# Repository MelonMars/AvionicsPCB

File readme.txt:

I think I'm doing this right, idk

2 Potentiometers: One is wind direction, other is wind intensity, max of 35 kts
LED Grid:
Top row is a turn coordinator, keep the white led in the middle, led moves in a direction that is prescriptives, use rudder coordinating with that side to correct a slip
Second from top row is altitude. Each dot is 1000 feet, going from dark to bright white, through grey for the altitude within 1000 feet
Next row is altitude in 10s of feet.
Altitudes are determined from barometric pressure, so are MSL and susceptible to temperature problems

Problem with the turn coordinator is idk how to actually have the turn coordinator figure out anything abt the turn. i BELIEVE that if the 3 axis accelerometer should be able to, as if it doesn't register a change while your turning, that means your CG(?) (I think CG is what the turn coordinator checks for slips, but once again I'm not sure) hasn't really changed, and you're going alright.

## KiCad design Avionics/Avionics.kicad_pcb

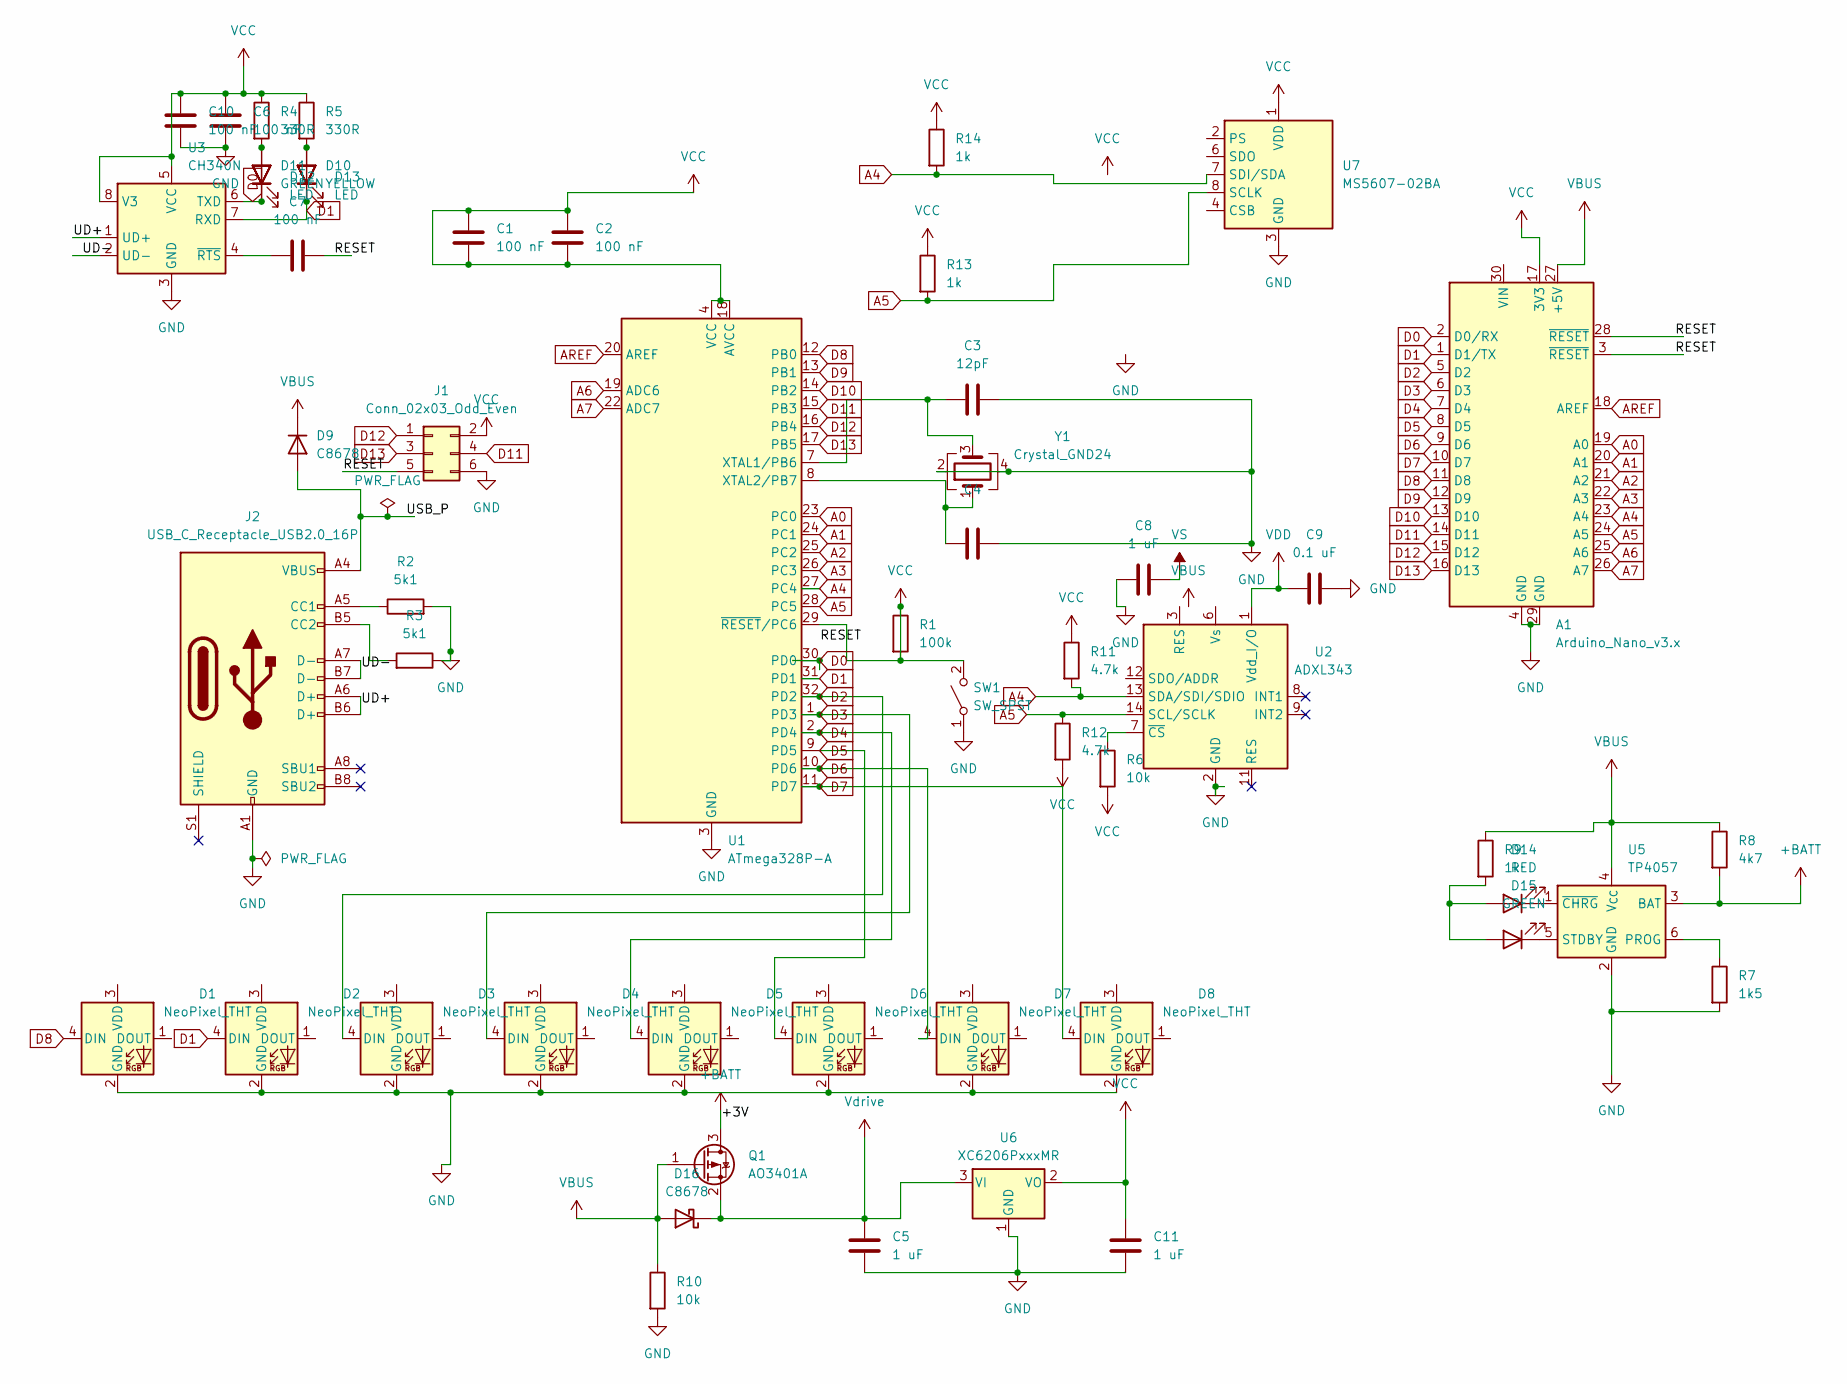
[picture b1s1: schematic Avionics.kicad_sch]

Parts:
A1: Arduino_Nano_v3.x; Arduino_Nano_WithMountingHoles
C1, C2, C6, C7, C10: 100 nF; C_0805_2012Metric_Pad1.18x1.45mm_HandSolder; LCSC C49678
C3, C4: 12pF; C_0805_2012Metric_Pad1.18x1.45mm_HandSolder; LCSC C1792
C5, C8, C11: 1 uF; C_0805_2012Metric_Pad1.18x1.45mm_HandSolder; LCSC C111768
C9: 0.1 uF; C_0805_2012Metric_Pad1.18x1.45mm_HandSolder; LCSC C49678
D1, D2, D3, D4, D5, D6, D7, D8: NeoPixel_THT; LED_WS2812_PLCC6_5.0x5.0mm_P1.6mm; LCSC C5378720
D9: C8678; D_SMC_Handsoldering; LCSC C8678
D10: YELLOW; D_SMC_Handsoldering; LCSC C2296
D11, D15: GREEN; D_1206_3216Metric_Pad1.42x1.75mm_HandSolder; LCSC C2297
D12, D13: LED; D_1206_3216Metric_Pad1.42x1.75mm_HandSolder; LCSC C2297
D14: RED; D_1206_3216Metric_Pad1.42x1.75mm_HandSolder; LCSC C101927
D16: C8678; D_SMA; LCSC C8678
J1: Conn_02x03_Odd_Even; PinHeader_2x03_P2.54mm_Vertical; LCSC C65114
J2: USB_C_Receptacle_USB2.0_16P; USB_C_Receptacle_Amphenol_12401548E4-2A; LCSC C2988369
Q1: AO3401A; SOT-23; LCSC C15127
R1: 100k; R_0805_2012Metric_Pad1.20x1.40mm_HandSolder; LCSC C101927
R2, R3: 5k1; R_0805_2012Metric_Pad1.20x1.40mm_HandSolder; LCSC C27834
R4, R5: 330R; R_0805_2012Metric_Pad1.20x1.40mm_HandSolder; LCSC C3016635
R6, R10: 10k; R_0805_2012Metric_Pad1.20x1.40mm_HandSolder; LCSC C17414
R7: 1k5; R_0805_2012Metric_Pad1.20x1.40mm_HandSolder; LCSC C416128
R8: 4k7; R_0805_2012Metric_Pad1.20x1.40mm_HandSolder; LCSC C2889530
R9, R13, R14: 1k; R_0805_2012Metric_Pad1.20x1.40mm_HandSolder; LCSC C17513
R11, R12: 4.7k; R_0805_2012Metric_Pad1.20x1.40mm_HandSolder; LCSC C245341
SW1: SW_SPST; SW_Push_1P1T_XKB_TS-1187A; LCSC C318884
U1: ATmega328P-A; TQFP-32_7x7mm_P0.8mm; LCSC C14877
U2: ADXL343; LGA-14_3x5mm_P0.8mm_LayoutBorder1x6y; LCSC C579453
U3: CH340N; SOP-8_3.9x4.9mm_P1.27mm; LCSC C2977777
U5: TP4057; TSOT-23-5; LCSC C725791
U6: XC6206PxxxMR; SOT-23-3; LCSC C2891841
U7: MS5607-02BA; LGA-8_3x5mm_P1.25mm; LCSC C97627
Y1: Crystal_GND24; Crystal_SMD_3225-4Pin_3.2x2.5mm_HandSoldering; LCSC C13738

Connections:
+BATT: Q1.3 (D), R8.2, U5.3 (BAT)
/RESET: A1.3 (~RESET), A1.28 (~RESET), C7.2, J1.5
/UD+: J2.A6 (D+), J2.B6 (D+), U3.1 (UD+)
/UD-: J2.A7 (D-), J2.B7 (D-), U3.2 (UD-)
/USB_P: D9.2 (A), J2.A4 (VBUS), J2.A9 (VBUS), J2.B4 (VBUS), J2.B9 (VBUS)
A0: A1.19 (A0), U1.23 (PC0)
A1: A1.20 (A1), U1.24 (PC1)
A2: A1.21 (A2), U1.25 (PC2)
A3: A1.22 (A3), U1.26 (PC3)
A4: A1.23 (A4), R11.2, R14.2, U1.27 (PC4), U2.13 (SDA/SDI/SDIO), U7.7 (SDI/SDA)
A5: A1.24 (A5), R12.1, R13.2, U1.28 (PC5), U2.14 (SCL/SCLK), U7.8 (SCLK)
A6: A1.25 (A6), U1.19 (ADC6)
A7: A1.26 (A7), U1.22 (ADC7)
AREF: A1.18 (AREF), U1.20 (AREF)
D0: A1.2 (D0/RX), D11.1 (K), D12.1 (K), U1.30 (PD0), U3.6 (TXD)
D1: A1.1 (D1/TX), D2.4 (DIN), D10.1 (K), D13.1 (K), U1.31 (PD1), U3.7 (RXD)
D2: A1.5 (D2), D3.4 (DIN), U1.32 (PD2)
D3: A1.6 (D3), D4.4 (DIN), U1.1 (PD3)
D4: A1.7 (D4), D5.4 (DIN), U1.2 (PD4)
D5: A1.8 (D5), D6.4 (DIN), U1.9 (PD5)
D6: A1.9 (D6), D7.4 (DIN), U1.10 (PD6)
D7: A1.10 (D7), D8.4 (DIN), U1.11 (PD7)
D8: A1.11 (D8), D1.4 (DIN), U1.12 (PB0)
D9: A1.12 (D9), U1.13 (PB1)
D10: A1.13 (D10), U1.14 (PB2)
D11: A1.14 (D11), J1.4, U1.15 (PB3)
D12: A1.15 (D12), J1.1, U1.16 (PB4)
D13: A1.16 (D13), J1.3, U1.17 (PB5)
GND: A1.4 (GND), A1.29 (GND), C3.2, C4.2, C5.2, C6.2, C8.1, C9.2, C10.2, C11.2, D1.2 (GND), D2.2 (GND), D3.2 (GND), D4.2 (GND), D5.2 (GND), D6.2 (GND), D7.2 (GND), D8.2 (GND), J1.6, J2.A1 (GND), J2.A12 (GND), J2.B1 (GND), J2.B12 (GND), R2.2, R3.1, R7.2, R10.2, SW1.1 (A), U1.3 (GND), U1.5 (GND), U1.21 (GND), U2.2 (GND), U2.4 (GND), U2.5 (GND), U3.3 (GND), U5.2 (GND), U6.1 (GND), U7.3 (GND), Y1.2, Y1.4
unnamed: D10.2 (A), D13.2 (A), R5.2
unnamed: D11.2 (A), D12.2 (A), R4.2
unnamed: D14.2 (A), D15.2 (A), R9.2
unnamed: D14.1 (K), U5.1 (~CHRG)
unnamed: D15.1 (K), U5.5 (STDBY)
unnamed: J2.A5 (CC1), R2.1
unnamed: J2.B5 (CC2), R3.2
unnamed: C3.1, U1.7 (XTAL1/PB6), Y1.3
unnamed: C4.1, U1.8 (XTAL2/PB7), Y1.1
unnamed: R6.1, U2.7 (~CS)
unnamed: C7.1, U3.4 (~RTS)
unnamed: R7.1, U5.6 (PROG)
unnamed: U7.4 (CSB), U7.5 (CSB)
VBUS: A1.27 (+5V), D9.1 (K), D16.2 (A), Q1.1 (G), R8.1, R9.1, R10.1, U5.4 (V_{CC})
VCC: A1.17 (3V3), C1.1, C1.2, C2.1, C2.2, C6.1, C10.1, C11.1, J1.2, R1.1, R1.2, R4.1, R5.1, R6.2, R11.1, R12.2, R13.1, R14.1, SW1.2 (B), U1.4 (VCC), U1.6 (VCC), U1.18 (AVCC), U1.29 (~RESET/PC6), U3.5 (VCC), U3.8 (V3), U6.2 (VO), U7.1 (VDD)
VDD: C9.1, U2.1 (Vdd_I/O)
VS: C8.2
Vdrive: C5.1, D16.1 (K), Q1.2 (S), U6.3 (VI)

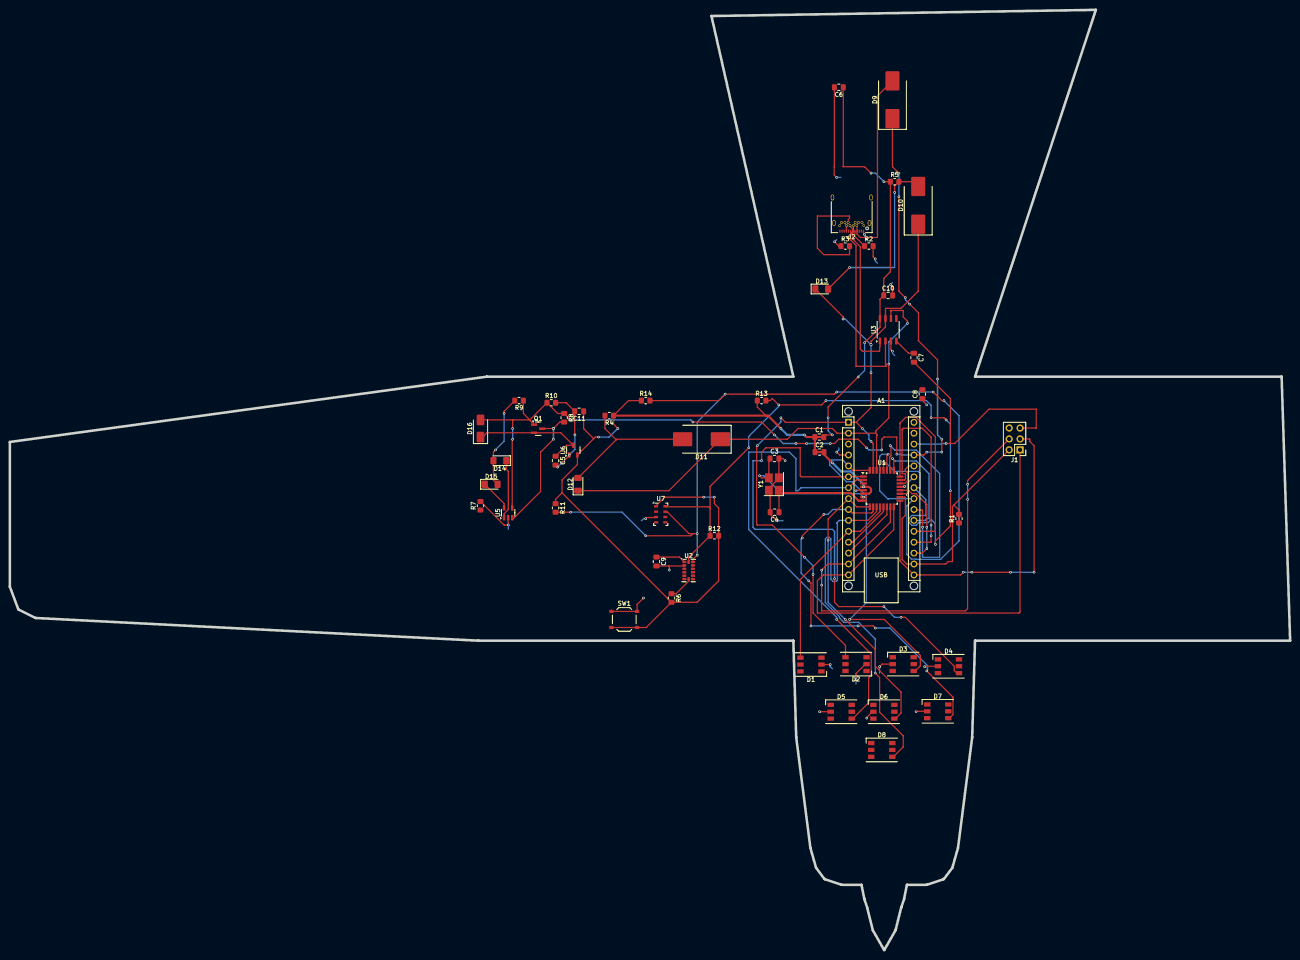
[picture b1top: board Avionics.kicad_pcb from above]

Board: 2 copper layers, 298.3 x 219.1 mm, 53 parts (0 on the bottom side), 45 nets.

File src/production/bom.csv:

Designator,Footprint,Quantity,Value,LCSC Part #
A1,Arduino_Nano_WithMountingHoles,1,Arduino_Nano_v3.x,
"C1, C10, C2, C6, C7",0805,5,100 nF,
"C11, C5, C8",0805,3,1 uF,
"C3, C4",0805,2,12pF,
C9,0805,1,0.1 uF,
"D1, D2, D3, D4, D5, D6, D7, D8",LED_WS2812_PLCC6_5.0x5.0mm_P1.6mm,8,NeoPixel_THT,
D10,D_SMC_Handsoldering,1,YELLOW,
D11,D_SMC_Handsoldering,1,GREEN,
"D12, D13",1206,2,LED,
D14,1206,1,RED,
D15,1206,1,GREEN,
D16,D_SMA,1,C8678,
D9,D_SMC_Handsoldering,1,C8678,
J1,PinHeader_2x03_P2.54mm_Vertical,1,Conn_02x03_Odd_Even,
J2,USB_C_Receptacle_Amphenol_12401548E4-2A,1,USB_C_Receptacle_USB2.0_16P,
Q1,SOT-23,1,AO3401A,
R1,0805,1,100k,
"R10, R6",0805,2,10k,
"R11, R12",0805,2,4.7k,
"R13, R14, R9",0805,3,1k,
"R2, R3",0805,2,5k1,
"R4, R5",0805,2,330R,
R7,0805,1,1k5,
R8,0805,1,4k7,
SW1,SW_Push_1P1T_XKB_TS-1187A,1,SW_SPST,
U1,TQFP-32_7x7mm_P0.8mm,1,ATmega328P-A,
U2,LGA-14_3x5mm_P0.8mm_LayoutBorder1x6y,1,ADXL343,
U3,SOP-8_3.9x4.9mm_P1.27mm,1,CH340N,
U5,TSOT-23-5,1,TP4057,
U6,SOT-23-3,1,XC6206PxxxMR,
U7,LGA-8_3x5mm_P1.25mm,1,MS5607-02BA,
Y1,Crystal_SMD_3225-4Pin_3.2x2.5mm_HandSoldering,1,Crystal_GND24,

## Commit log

2024-07-09 First Hour
    Think I've done a decent amount. I don't really get too much of this tho. It's like, I think I connected everything, but idk if I actually did (I hope I did), and idk if it all is gonna work the righ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
2024-07-09 Started moving to KiCad
    Had to finish early bc stuff.
    KiCAD is MUCH MUCH smoother
2024-07-10 Hour 2
    Designed PCB from Schematic (I think it works)
    Adding accelerometer (Still need to connect it)
    Adding LEDs
2024-07-10 3hr
    very tired
2024-07-10 3 hr
    Added barometer / altimeter, battery, arduino pinout
2024-07-11 Another hour
    Finished up the schematic (at least I hope) & started working (~ 1/2 way done), with the actual PCB layout.
2024-07-16 Anothrt hr
2024-07-16 Almost done
    Basically just need to convert everything to JLCPCB components now, and then I should be good to go.
2024-07-16 FINISHED
    Final assignments, and shrinked board.
2024-07-25 1/2 hr
    Spent a lot of time fiddling with JLCPCB, before deciding to use OSHPark
